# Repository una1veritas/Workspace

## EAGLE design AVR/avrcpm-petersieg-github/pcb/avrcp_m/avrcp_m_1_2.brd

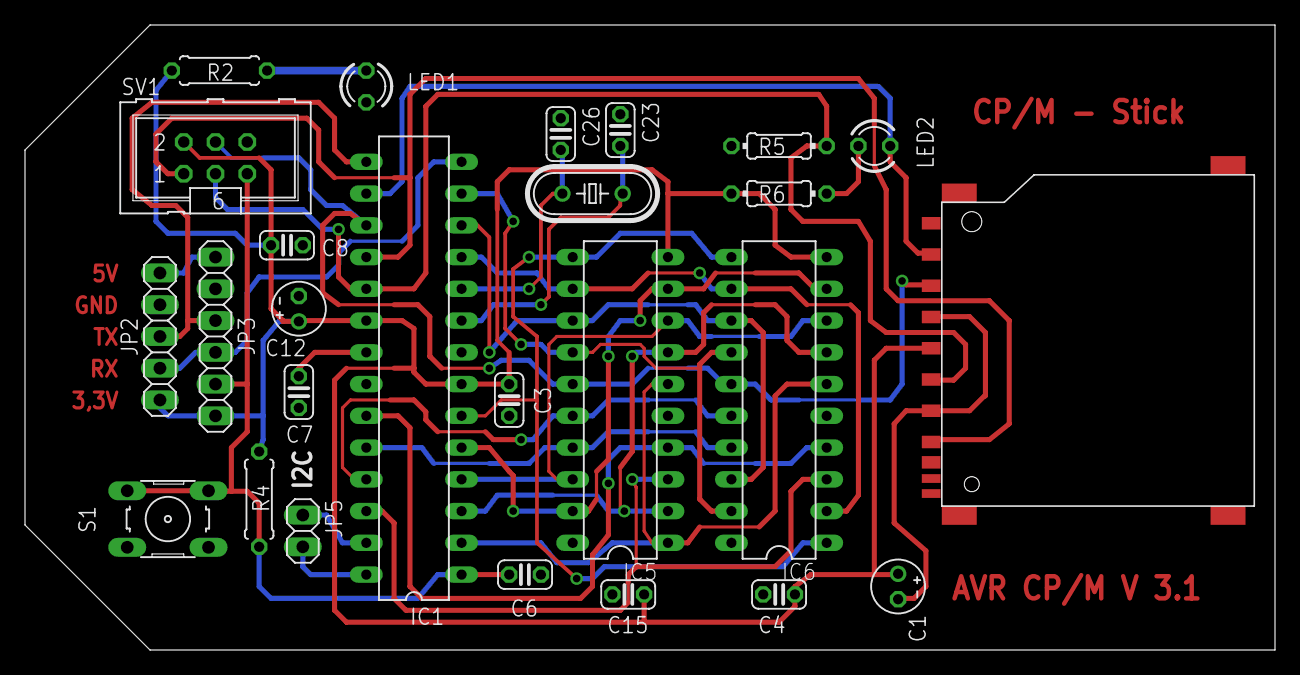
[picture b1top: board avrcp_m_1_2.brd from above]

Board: 2 copper layers, 100.0 x 50.0 mm, 26 parts (0 on the bottom side), 29 nets.

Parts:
C1: 4,7µ; E2-4
C3, C4, C6, C7, C8, C15: 100n; C025-024X044
C12: 10µ; E2-4
C23, C26: 27p; C025-024X044
CON2: SDCMF-109XXW010SDCMF-10915W0T1_SO; SDCMF-10915W0T1
IC1: ATmega168; DIL28-3
IC5, IC6: 4256; DIL20
JP2: 1X05
JP3: 1X06
JP5: 1X02
LED1: Grün; LED3MM
LED2: Gelb; LED3MM
Q1: 20 MHz; HC49/S
R2: 330; 0207/7
R4: 10k; 0207/7
R5: 10k; 0204/7
R6: 330; 0204/7
S1: Reset; B3F-10XX
SV1: ISP; ML6

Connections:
+3V3: C1.+, C3.1, C4.2, C8.1, C12.+, C15.2, CON2.P4, IC1.7, IC1.20, IC5.10, IC6.10, JP2.1, JP3.1, R2.2, R4.1, R6.2, SV1.2
+5V: JP2.5, JP3.6
/CAS: IC1.24, IC5.17, IC6.17
/OE: IC1.25, IC5.16, IC6.16
/RAS: IC1.23, IC5.4, IC6.4
/WE: IC1.26, IC5.3, IC6.3
CS: CON2.P1, IC1.16, LED2.K
D0_A0: IC1.2, IC5.1, IC5.6, IC6.6
D1_A1: IC1.3, IC5.2, IC5.7, IC6.7
D2_A2: IC1.4, IC5.8, IC5.18, IC6.8
D3_A3: IC1.5, IC5.9, IC5.19, IC6.9
D4_A4: IC1.6, IC5.11, IC6.1, IC6.11
D5_A5: IC1.11, IC5.12, IC6.2, IC6.12
D6_A6: IC1.12, IC5.13, IC6.13, IC6.18
D7_A7: IC1.13, IC5.14, IC6.14, IC6.19
GND: C1.-, C3.2, C4.1, C6.1, C7.2, C8.2, C12.-, C15.1, C23.2, C26.2, CON2.P3, CON2.P6, IC1.8, IC1.22, IC5.20, IC6.20, JP2.4, JP3.5, LED1.K, R5.2, S1.1, S1.2, SV1.6
MISO_A9: CON2.P7, IC1.18, SV1.1
MOSI_A8: CON2.P2, IC1.17, IC5.15, IC6.15, SV1.4
unnamed: C7.1, IC1.21
unnamed: IC1.27, JP5.1
unnamed: IC1.28, JP5.2
unnamed: LED1.A, R2.1
unnamed: LED2.A, R6.1
unnamed: C26.1, IC1.10, Q1.1
unnamed: C23.1, IC1.9, Q1.2
RESET_CPM: C6.2, IC1.1, JP3.2, R4.2, S1.3, S1.4, SV1.5
RXD_AVR: IC1.14, JP2.2, JP3.3
SCK_A10: CON2.P5, IC1.19, R5.1, SV1.3
TXD_AVR: IC1.15, JP2.3, JP3.4

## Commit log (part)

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2021-08-27 radix sort
2021-08-30 tmp117
2021-09-06 qwiic
2021-09-09 dfa.c
2021-09-10 nfa.c
2021-09-12 veml
2021-09-12 stemmaqt
2021-09-19 json
2021-09-25 json2csv
2021-10-01 dfa.c 2021101.1
2021-10-01 dfa, nfa
2021-10-09 csv
    csv
2021-10-10 puzzle
2021-10-10 typoppoy
2021-10-17 weather
2021-10-18 cutils
2021-11-08 PyPuzzleSolver
2021-11-09 solved
2021-11-11 make table
2021-11-11 table maker
2021-11-16 bitsetmap
2021-11-19 bytearray
2021-11-19 sudoku
2021-11-19 arraysudoku new solve
2021-12-13 PyNFC
2021-12-13 blaster
2022-01-04 lastlogreader
2022-01-17 sudokusolver
2022-01-22 solver
2022-01-23 sudoku solver
2022-01-23 copy
2022-02-08 fibo
2022-02-28 pypuzzle
2022-02-28 main
2022-03-29 picalc
2022-04-12 type-cast
2022-04-28 pyjong
2022-05-10 list
2022-05-10 test
2022-05-10 smfscorereader
2022-05-10 smf::
2022-05-12 player
2022-05-14 simplay
2022-05-26 main.cpp
2022-06-03 5.log
2022-06-03 moodle blaster
2022-06-08 split
2022-08-04 decisiontree
2022-08-22 sieve
2022-09-15 dfa/nfa moved
2022-10-19 makefile
2023-02-28 curl-yajl
2023-04-11 julian
2023-07-05 forcast
2023-08-23 tablemaker4
2023-08-24 table maker 4
2023-11-07 primes
2023-11-21 LCBlaster
2024-01-20 abstract_extraction
2024-01-20 PDF Collector
2024-01-20 pypdf test
2024-01-21 openpyxl
2024-01-23 Blasters
2024-01-23 XSLX
2024-01-23 PyExcel
2024-01-23 sample
2024-02-16 pypdf
2024-02-18 feedback
2024-02-19 feedbackmaker
2024-02-19 perfevaluation
2024-02-20 separator
2024-02-22 remove csv
2024-02-29 collector
2024-02-29 libsense
2024-06-09 pygroupphoto
2024-06-10 vba example
2024-11-25 sotsuken
2024-11-26 cppHash
2024-11-26 cppHash, pysotsuken
2024-11-27 bygpa
2024-12-01 bydesire
2024-12-02 comb
2024-12-15 geomnetric objects
2024-12-27 automata
2025-01-17 intension survey
2025-01-20 survey
2025-01-20 pysotsuken
2025-01-21 pysotsu
2025-02-14 pigpio
2025-02-17 temp
2025-02-17 move to private
2025-02-17 moved
2025-02-18 lcu blasters
2025-02-19 .pydev
2025-02-19 lcu removed
2025-03-12 pytts
2025-03-18 gitignore
2025-04-03 pytexttospeech
2025-04-03 websocket
2025-04-03 websockets
2025-04-03 demo
2025-04-05 text to speerch
2025-04-05 openai removed
2025-04-18 html
2025-04-18 hub cover
2025-04-24 asyncio
2025-04-29 json example
2025-05-06 VBA 成績不振学生チェック
2025-05-07 チェック
2025-05-08 Revert "チェック"
    This reverts commit 1b406fb92260732e7947cf118222d3c3613aef4a.
2025-05-08 修得単位数チェック
2025-05-08 backup
2025-05-08 vector, dictionary ,list
2025-09-05 printf
2025-09-12 6502 woz mon
2025-09-16 basic_io
2025-09-20 "40.60" succeed
2025-09-20 asciiart_c
2025-09-29 basic io test
2025-10-07 emuz80
2025-10-17 decision tree
2025-10-20 py decision tree
2025-10-27 pyhub
2025-10-27 pyhubcover
2025-10-28 must be checked the lexicographical order
2025-10-28 pending
2025-10-28 dfs enumeration
2025-11-05 uart
2025-11-07 py hub cover
2025-11-10 hubc
2025-11-10 undirected graph
2025-11-12 random graph
2025-11-17 KeyError: None
2025-11-17 local search
2025-11-19 pyhubcover graph stats()
2025-11-20 mez88
2025-11-20 abehubcover
2025-11-20 MEZ88 removed
2025-11-28 hub cover debug __eq__
2025-11-28 settings
2025-11-29 usbasp adjuswted for compilation
2025-12-01 6502
2025-12-03 emu80
2025-12-05 uart interrupt driven
2025-12-05 mplabx
2025-12-05 mplabx interrupt tx and polling tx
2025-12-07 ehbasic
2025-12-11 wozmon with acia
2025-12-14 trapped
2025-12-14 emuz 6502
2025-12-14 recovery
2025-12-14 remove
2025-12-14 PROJ
2025-12-14 X proj
2025-12-14 ignore
2025-12-14 once remove projects
2025-12-14 memcheck and transfer tweaked
2025-12-14 ignore file
2025-12-14 suspected bug
2025-12-14 debug
2025-12-14 main.c
2025-12-15 ちょっと心配
2025-12-15 min_mon
2025-12-16 6502/65816
2025-12-18 emuz
2025-12-18 acia and constant redefined
2025-12-19 recovered
2025-12-19 config bit setting added to config.h to avoid warnings
2025-12-19 だいじょうぶそう。
2025-12-20 ACIA の挙動を修正したらうまくいっているような気がする
2025-12-20 今のところ大丈夫だが。。
2025-12-20 20 hours ago mereged
2025-12-20 だいじょうぶなんかなぁ。。
2025-12-20 Seems B000 ACIA going well...
2025-12-20 Still seems well.
    ACIA from B000 in 6551 Style, ACIAout is now checking TDRE.
2025-12-20 makefile tweaked.
2025-12-20 直接書き出した rom.c を使うようにした
2025-12-21 問題は生じていないようだ
2025-12-21 wozmon
2025-12-22 ehbasic with wozmon from FE00 (min mon from EA00)
2025-12-22 table of baud rate coefficients
2025-12-27 68k8ram+spi test
2025-12-28 Exhausted.
2025-12-28 UART3 Interrupt Rx and IVT sample code
2025-12-29 6502 just before branching
2025-12-29 NOUART
2025-12-29 SRAM_READ/WRITE provided
2025-12-29 つかれた。。
2026-01-01 mplab
2026-01-02 snap
2026-01-03 gpio
2026-01-03 typed char lit LED
2026-01-03 uart3
2026-01-04 py murmur
2026-01-04 shuffle
2026-01-04 shuffle16
2026-01-05 tic tac
2026-01-06 pin out
2026-01-11 F47Q43 workng
2026-01-12 commented
2026-01-12 macro
2026-01-12 68k8 board never works...
2026-01-14 melkman's algiorithm, the first challenge
2026-01-16 SRAM_Check
2026-01-16 MPLAB X Proj
2026-01-17 SRAM check seems working well with rom load and read checks.
2026-01-17 memory check and transfer to sram is aggregated
2026-01-18 working,
2026-01-26 EMUZQ43 W65C02
2026-01-28 comment corrected
2026-03-06 gave up 68030, 6809 ram is not working
2026-03-06 placed 6809 original code
2026-03-07 ignoreignore file
2026-03-09 6809 main
2026-03-09 CLC Test
2026-03-24 rewriting
2026-03-28 ffwd
2026-03-28 rmoved
2026-04-07 asm09
2026-04-08 mirage-asm09
2026-04-10 as9 is now running...
2026-04-11 stdbool
2026-04-11 Introduced stdbool.h, true & false
2026-04-11 free_symtab function added.
2026-04-11 search_h
2026-04-30 srec
2026-05-06 sdp puzzling
2026-05-08 operator = and type() override test
2026-05-15 emuz80 cpm unstable
2026-05-29 organize
2026-06-07 java test
2026-06-18 java
2026-06-30 wdrop
